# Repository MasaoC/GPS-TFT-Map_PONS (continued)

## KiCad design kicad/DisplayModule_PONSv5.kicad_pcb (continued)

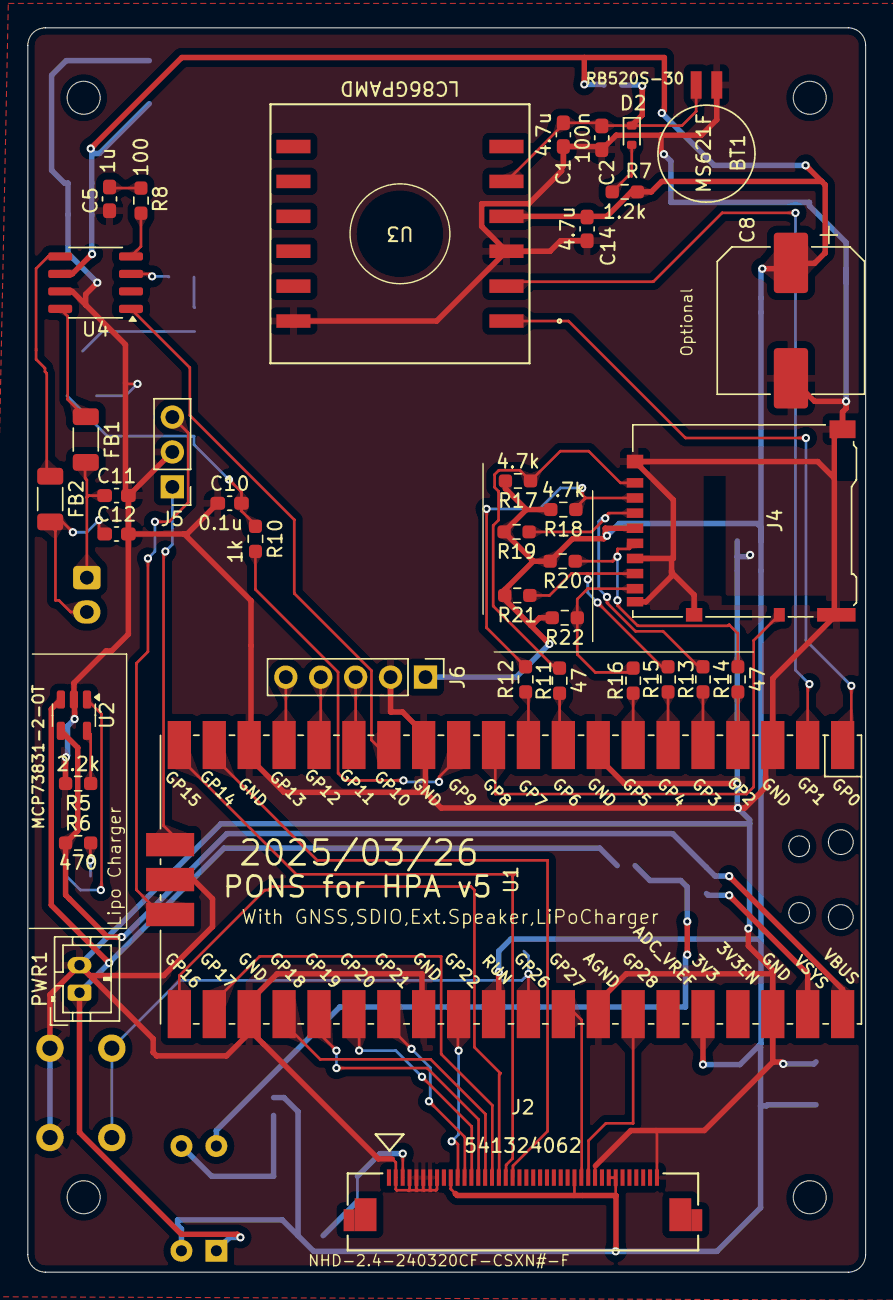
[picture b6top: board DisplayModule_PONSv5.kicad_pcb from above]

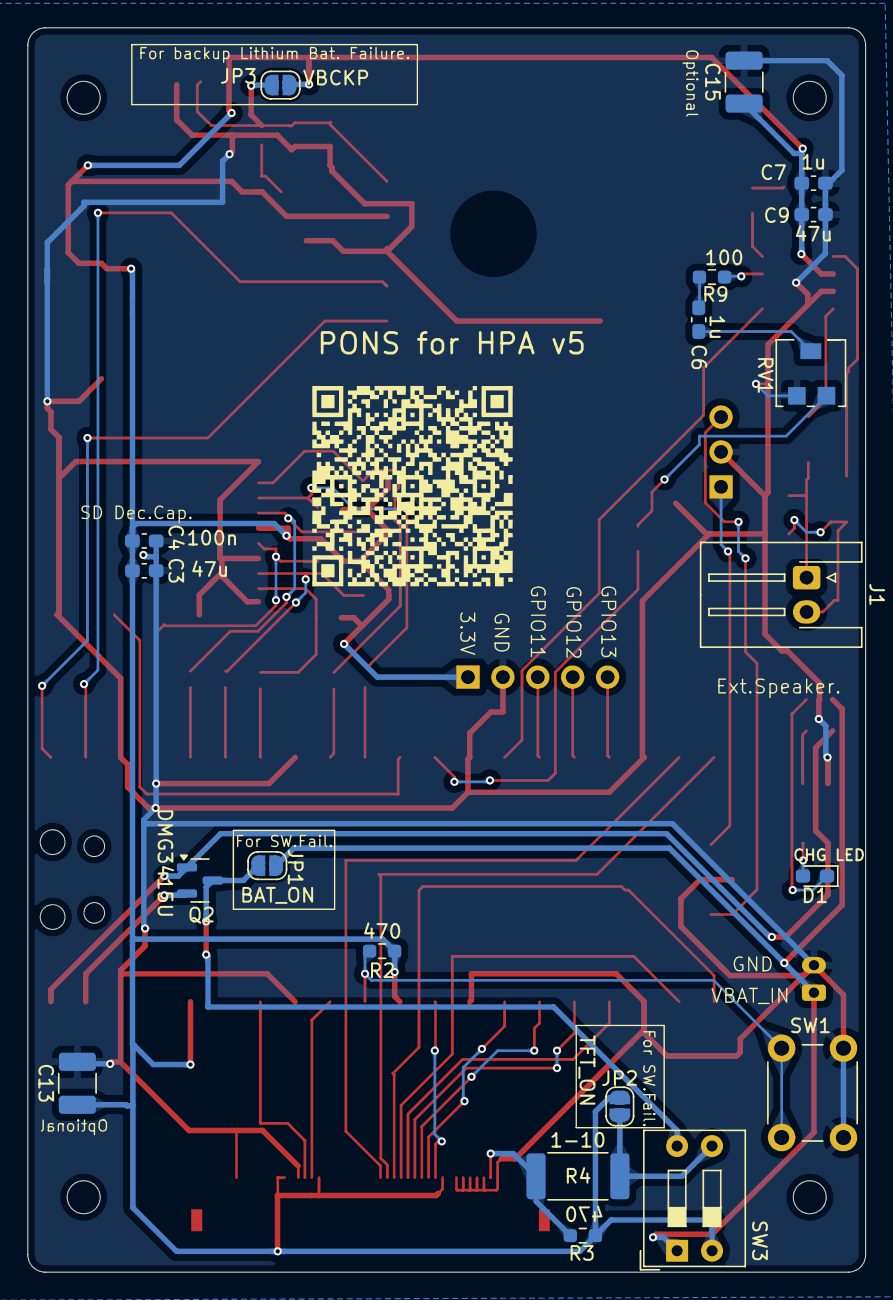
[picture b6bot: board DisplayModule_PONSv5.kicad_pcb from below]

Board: 2 copper layers, 61.0 x 90.5 mm, 58 parts (20 on the bottom side), 57 nets.

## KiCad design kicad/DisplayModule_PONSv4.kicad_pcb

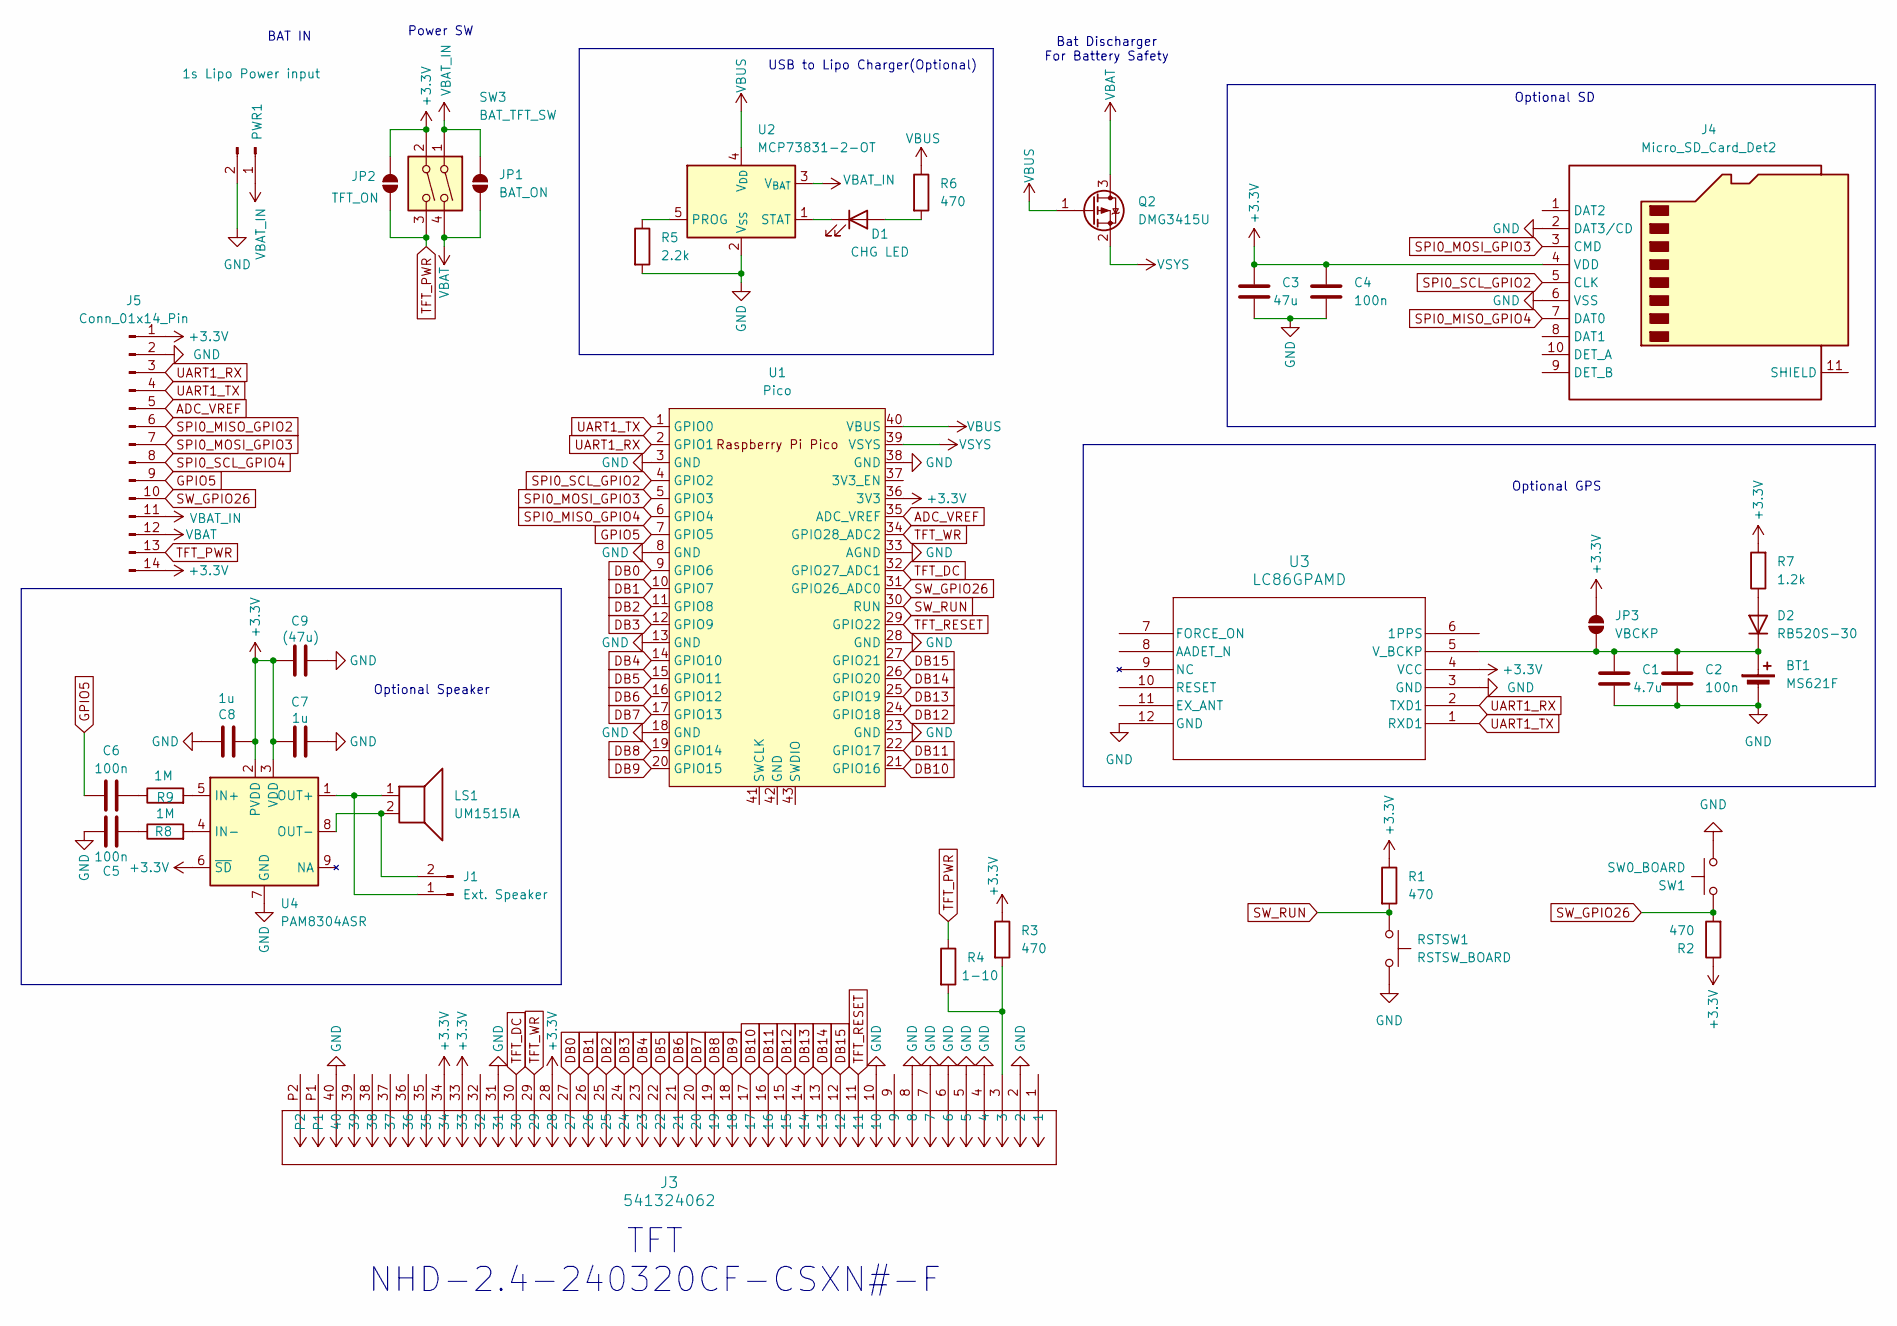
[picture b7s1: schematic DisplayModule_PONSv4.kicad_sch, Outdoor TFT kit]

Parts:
BT1: MS621F; BatteryHolder_Seiko_MS621F
C1: 4.7u; C_0603_1608Metric_Pad1.08x0.95mm_HandSolder
C2, C4, C5, C6: 100n; C_0603_1608Metric_Pad1.08x0.95mm_HandSolder
C3: 47u; C_0603_1608Metric_Pad1.08x0.95mm_HandSolder
C7, C8: 1u; C_0603_1608Metric_Pad1.08x0.95mm_HandSolder
C9: (47u); C_0603_1608Metric_Pad1.08x0.95mm_HandSolder
D1: CHG LED; LED_0603_1608Metric_Pad1.05x0.95mm_HandSolder
D2: RB520S-30; D_SOD-523
J1: Ext. Speaker; JST_XA_B02B-XASK-1_1x02_P2.50mm_Vertical
J3: 541324062; CON_541324062_MOL
J4: Micro_SD_Card_Det2; microSD_HC_Hirose_DM3AT-SF-PEJM5
J5: Conn_01x14_Pin; PinHeader_1x14_P2.54mm_Vertical
JP1: BAT_ON; SolderJumper-2_P1.3mm_Open_RoundedPad1.0x1.5mm
JP2: TFT_ON; SolderJumper-2_P1.3mm_Open_RoundedPad1.0x1.5mm
JP3: VBCKP; SolderJumper-2_P1.3mm_Open_RoundedPad1.0x1.5mm
LS1: UM1515IA; UM1515IA085008
PWR1: 1s Lipo Power input; JST_PH_B2B-PH-K_1x02_P2.00mm_Vertical
Q2: DMG3415U; SOT-23
R1, R2, R3, R6: 470; R_0603_1608Metric_Pad0.98x0.95mm_HandSolder
R4: 1-10; R_2512_6332Metric_Pad1.40x3.35mm_HandSolder
R5: 2.2k; R_0603_1608Metric_Pad0.98x0.95mm_HandSolder
R7: 1.2k; R_0603_1608Metric_Pad0.98x0.95mm_HandSolder
R8, R9: 1M; R_0603_1608Metric_Pad0.98x0.95mm_HandSolder
RSTSW1: RSTSW_BOARD; TVAF06-A020B-R
SW1: SW0_BOARD; SW_PUSH_6mm_H9.5mm
SW3: BAT_TFT_SW; SW_DIP_SPSTx02_Slide_9.78x7.26mm_W7.62mm_P2.54mm
U1: Pico; RPi_Pico_SMD
U2: MCP73831-2-OT; SOT-23-5
U3: LC86GPAMD; L86_QWS
U4: PAM8304ASR; MSOP-8-1EP_3x3mm_P0.65mm_EP1.5x1.8mm

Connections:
+3.3V: C3.1, C4.1, C7.1, C8.1, C9.1, J3.28, J3.33, J3.34, J4.4 (VDD), J5.1, J5.14, JP2.2 (B), JP3.1 (A), R1.1, R2.1, R3.1, R7.2, SW3.2, U1.36 (3V3), U3.4 (VCC), U4.2 (PVDD), U4.3 (VDD), U4.6 (~SD)
ADC_VREF: J5.5, U1.35 (ADC_VREF)
DB0: J3.27, U1.9 (GPIO6)
DB1: J3.26, U1.10 (GPIO7)
DB2: J3.25, U1.11 (GPIO8)
DB3: J3.24, U1.12 (GPIO9)
DB4: J3.23, U1.14 (GPIO10)
DB5: J3.22, U1.15 (GPIO11)
DB6: J3.21, U1.16 (GPIO12)
DB7: J3.20, U1.17 (GPIO13)
DB8: J3.19, U1.19 (GPIO14)
DB9: J3.18, U1.20 (GPIO15)
DB10: J3.17, U1.21 (GPIO16)
DB11: J3.16, U1.22 (GPIO17)
DB12: J3.15, U1.24 (GPIO18)
DB13: J3.14, U1.25 (GPIO19)
DB14: J3.13, U1.26 (GPIO20)
DB15: J3.12, U1.27 (GPIO21)
GND: BT1.2 (-), C1.2, C2.2, C3.2, C4.2, C5.1, C7.2, C8.2, C9.2, J3.2, J3.4, J3.5, J3.6, J3.7, J3.8, J3.10, J3.31, J3.40, J4.2 (DAT3/CD), J4.6 (VSS), J5.2, PWR1.2, R5.2, RSTSW1.2, SW1.2, U1.3 (GND), U1.8 (GND), U1.13 (GND), U1.18 (GND), U1.23 (GND), U1.28 (GND), U1.33 (AGND), U1.38 (GND), U2.2 (V_{SS}), U3.3 (GND), U3.12 (GND), U4.7 (GND)
GPIO5: C6.1, J5.9, U1.7 (GPIO5)
unnamed: BT1.1 (+), C1.1, C2.1, D2.1 (K), JP3.2 (B), U3.5 (V_BCKP)
unnamed: C5.2, R8.1
unnamed: C6.2, R9.1
unnamed: D1.2 (A), R6.2
unnamed: D1.1 (K), U2.1 (STAT)
unnamed: D2.2 (A), R7.1
unnamed: J1.1, LS1.1, U4.1 (OUT+)
unnamed: J1.2, LS1.2, U4.8 (OUT-)
unnamed: J3.3, R3.2, R4.2
unnamed: R5.1, U2.5 (PROG)
unnamed: R9.2, U4.5 (IN+)
unnamed: R8.2, U4.4 (IN-)
SPI0_MISO_GPIO2: J5.6
SPI0_MISO_GPIO4: J4.7 (DAT0), U1.6 (GPIO4)
SPI0_MOSI_GPIO3: J4.3 (CMD), J5.7, U1.5 (GPIO3)
SPI0_SCL_GPIO2: J4.5 (CLK), U1.4 (GPIO2)
SPI0_SCL_GPIO4: J5.8
SW_GPIO26: J5.10, R2.2, SW1.1, U1.31 (GPIO26_ADC0)
SW_RUN: R1.2, RSTSW1.1, U1.30 (RUN)
TFT_DC: J3.30, U1.32 (GPIO27_ADC1)
TFT_PWR: J5.13, JP2.1 (A), R4.1, SW3.3
TFT_RESET: J3.11, U1.29 (GPIO22)
TFT_WR: J3.29, U1.34 (GPIO28_ADC2)
UART1_RX: J5.3, U1.2 (GPIO1), U3.2 (TXD1)
UART1_TX: J5.4, U1.1 (GPIO0), U3.1 (RXD1)
VBAT: J5.12, JP1.2 (B), Q2.3 (D), SW3.4
VBAT_IN: J5.11, JP1.1 (A), PWR1.1, SW3.1, U2.3 (V_{BAT})
VBUS: Q2.1 (G), R6.1, U1.40 (VBUS), U2.4 (V_{DD})
VSYS: Q2.2 (S), U1.39 (VSYS)

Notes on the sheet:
Optional SD
Optional GPS
USB to Lipo Charger(Optional)
Bat Discharger For Battery Safety
BAT IN
Optional Speaker
Power SW
TFT NHD-2.4-240320CF-CSXN#-F

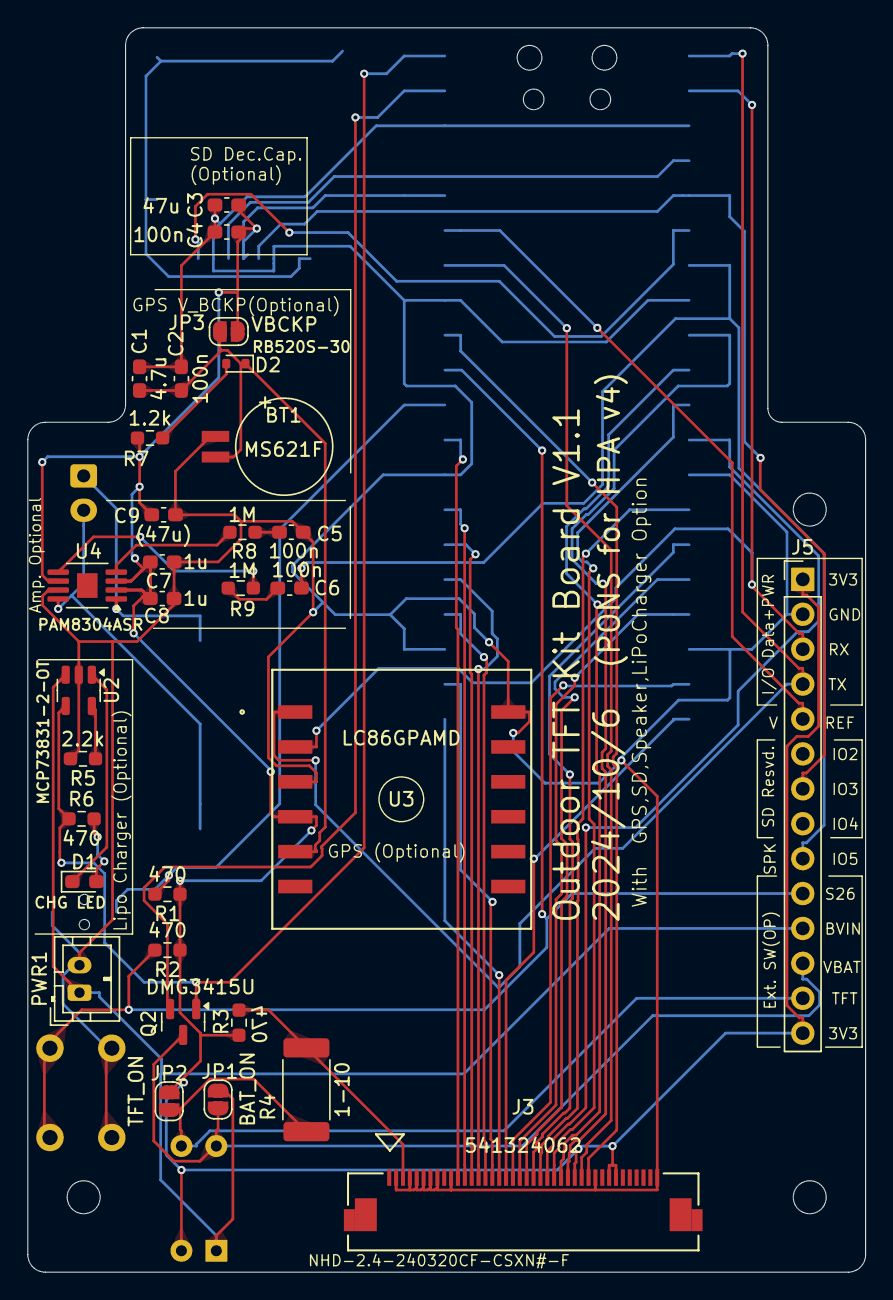
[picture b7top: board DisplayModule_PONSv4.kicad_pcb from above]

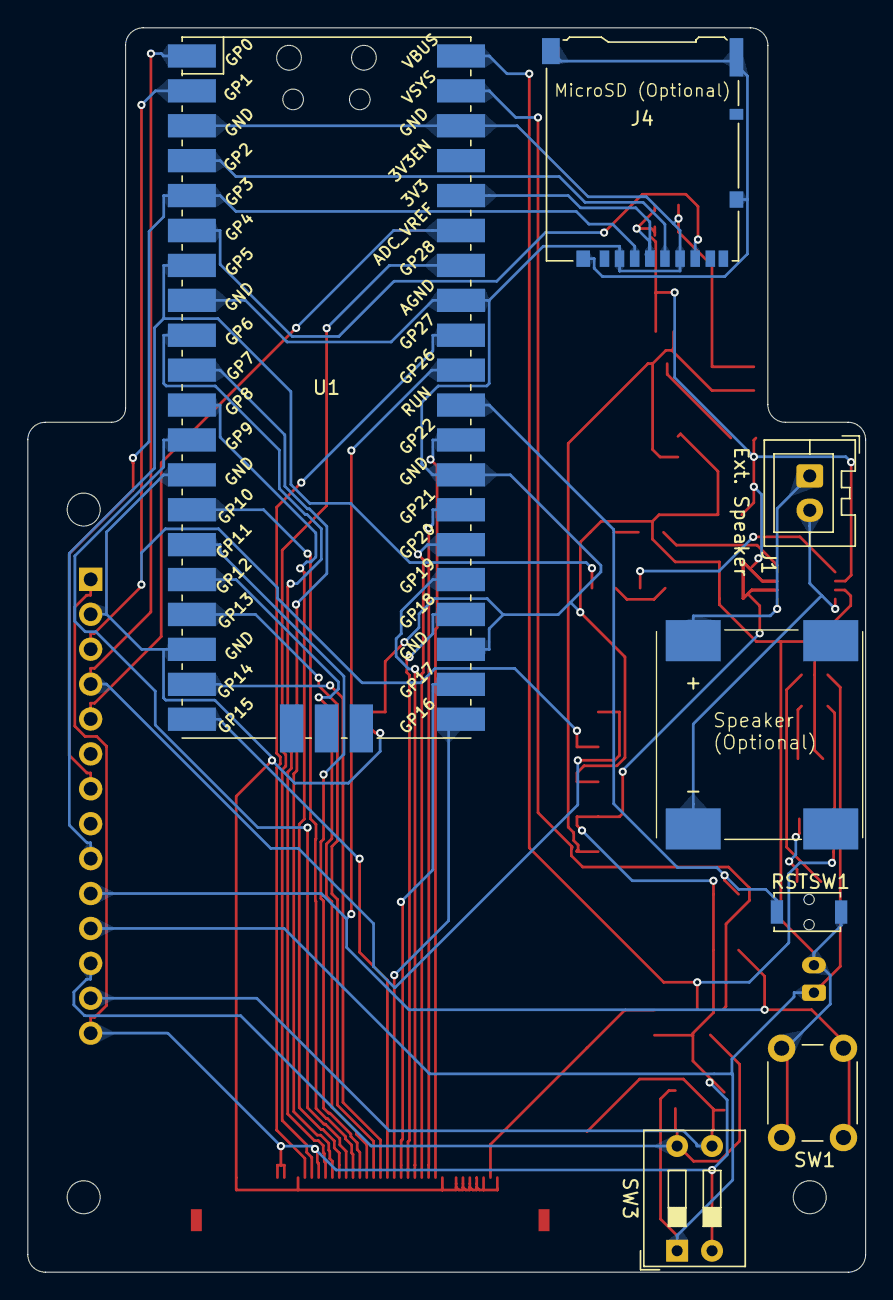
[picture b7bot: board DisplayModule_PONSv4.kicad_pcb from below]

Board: 2 copper layers, 61.0 x 90.5 mm, 38 parts (7 on the bottom side), 47 nets.

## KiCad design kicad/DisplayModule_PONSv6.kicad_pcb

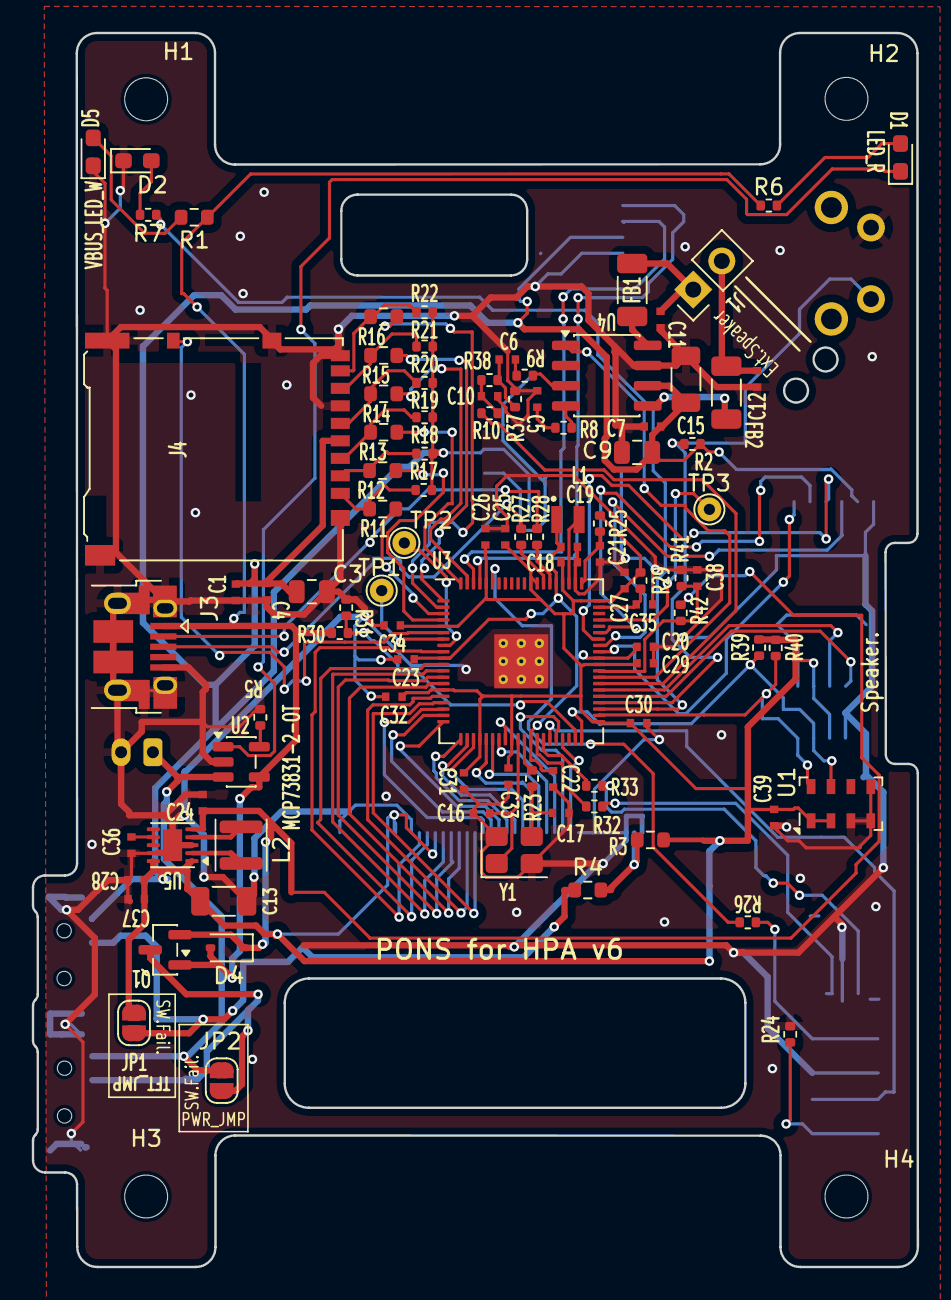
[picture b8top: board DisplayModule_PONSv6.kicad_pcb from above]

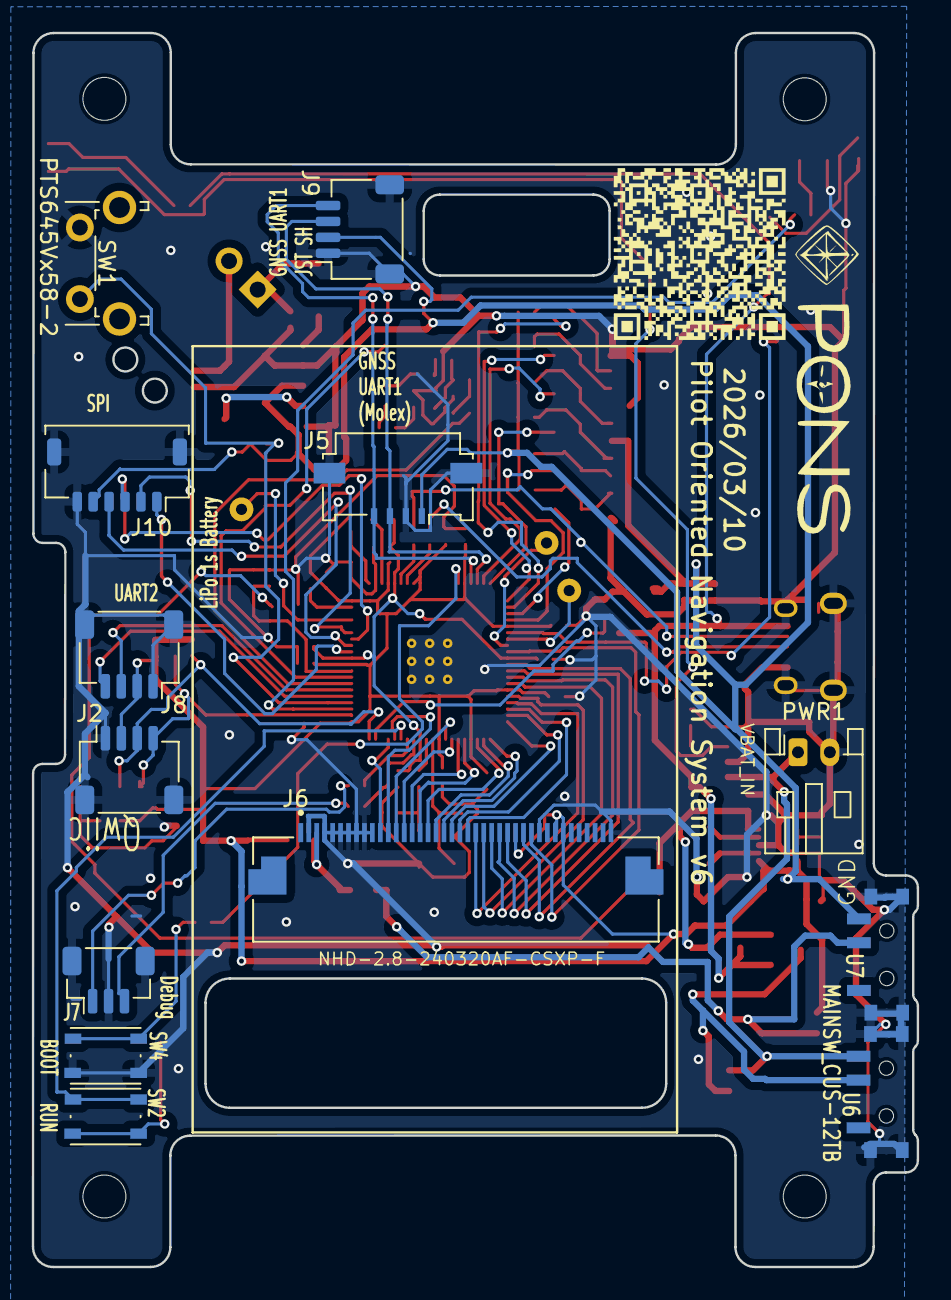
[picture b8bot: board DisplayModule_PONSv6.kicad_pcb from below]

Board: 2 copper layers, 55.6 x 77.6 mm, 115 parts (13 on the bottom side), 96 nets.

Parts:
C1, C5, C6, C7, C38: 1u; C_0402_1005Metric_small_pads
C3, C9: 47u; C_0805_2012Metric
C4, C10, C20, C23, C25, C26, C27, C29, C30, C31, C32, C33, C34, C36, C39: 100n; C_0402_1005Metric_small_pads
C11, C12: 220p; C_0402_1005Metric_small_pads
C13, C15: 100u; C_1206_3216Metric
C16, C17: 33p; C_0402_1005Metric_small_pads
C18, C19, C21, C22, C24, C35: 4.7u; C_0402_1005Metric_small_pads
C28, C37: 10u; C_0402_1005Metric_small_pads
D1, D2: LED_R; LED_0603_1608Metric_Pad1.05x0.95mm_HandSolder
D4: 1N5819WS; D_SOD-323
D5: VBUS_LED_W; LED_0603_1608Metric_Pad1.05x0.95mm_HandSolder
FB1, FB2: 390; L_1206_3216Metric_Pad1.22x1.90mm_HandSolder
H1, H2, H3, H4: MountingHole; MountingHole_2.7mm_M2.5
J1: Ext. Speaker; PinHeader_1x02_P2.54mm_Vertical
J2, J9: Conn_01x04_MountingPin; JST_SH_SM04B-SRSS-TB_1x04-1MP_P1.00mm_Horizontal
J3: USB_B_Micro; USB_Micro-B_Amphenol_10103594-0001LF_Horizontal
J4: Micro_SD_Card_Det2; microSD_HC_Hirose_DM3AT-SF-PEJM5
J5: 2005280040; Molex_200528-0040_1x04-1MP_P1.00mm_Horizontal
J6: 54132-4062; MOLEX_54132-4062
J7: Conn_01x03_Shielded; JST_SH_BM03B-SRSS-TB_1x03-1MP_P1.00mm_Vertical
J8: Conn_01x04_Shielded; JST_SH_SM04B-SRSS-TB_1x04-1MP_P1.00mm_Horizontal
J10: Conn_01x05_MountingPin; JST_SHL_SM06B-SHLS-TF_1x06-1MP_P1.00mm_Horizontal
JP1: TFT_JMP; SolderJumper-2_P1.3mm_Open_RoundedPad1.0x1.5mm
JP2: PWR_JMP; SolderJumper-2_P1.3mm_Open_RoundedPad1.0x1.5mm
L1: 3.3u; L_pol_2016
L2: 1.5u; L_APV_ANR3015
PWR1: 1s Lipo Power input; JST_PH_S2B-PH-K_1x02_P2.00mm_Horizontal
Q1: AO3401A; SOT-23
R1, R3: 470; R_0603_1608Metric
R2: 470; R_0402_1005Metric
R4: 1; R_0603_1608Metric
R5: 2.2k; R_0402_1005Metric
R6, R7, R29: 200; R_0402_1005Metric
R8, R9, R32, R33: 100; R_0402_1005Metric
R10, R23, R24, R26, R38: 1k; R_0402_1005Metric
R11, R12, R13, R14, R15, R16: 47; R_0603_1608Metric
R17, R18, R19, R20, R21, R22, R39, R40: 4.7k; R_0402_1005Metric
R25: 33; R_0402_1005Metric
R27, R28: 22; R_0402_1005Metric
R30: 5K1; R_0402_1005Metric
R31: 10K; R_0402_1005Metric
R37: 10k; R_0402_1005Metric
R41: 51K; R_0402_1005Metric
R42: 100K; R_0402_1005Metric
SW1: PTS645Vx58-2; SW_Tactile_SPST_Angled_PTS645Vx58-2LFS
SW2: SW_Push_RUN; SW_Push_1P1T_NO_Vertical_Wuerth_434133025816
SW4: SW_Push_BOOT; SW_Push_1P1T_NO_Vertical_Wuerth_434133025816
TP1, TP2, TP3: TestPoint; TestPoint_THTPad_D1.5mm_Drill0.7mm
U1: MS5611-01BA; LGA-8_3x5mm_P1.25mm
U2: MCP73831-2-OT; SOT-23-5
U3: RP2350_80QFN; RP2350-QFN-80-1EP_10x10_P0.4mm_EP3.4x3.4mm_ThermalVias
U4: PAM8302AAD; SO-8_3.9x4.9mm_P1.27mm
U5: TPS63031DSK; WSON-10-1EP_2.5x2.5mm_P0.5mm_EP1.2x2mm
U6: MAINSW_CUS-12TB; CUS-12B
U7: TFTSW_CUS-12TB; CUS-12B
Y1: X322512MSB4SI; Crystal_SMD_3225-4Pin_3.2x2.5mm

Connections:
+1V1: C19.1, C20.1, C22.1, C23.1, L1.1, U3.10 (DVDD), U3.32 (DVDD), U3.51 (DVDD), U3.65 (VREG_FB)
+3V3: C1.1, C3.1, C4.1, C7.1, C9.1, C13.1, C15.1, C18.1, C25.1, C26.1, C27.1, C28.1, C29.1, C30.1, C31.1, C32.1, C33.1, C34.1, C37.1, C39.1, J2.2, J4.4 (VDD), J5.1, J6.28, J6.33, J6.34, J8.2, J9.2, J10.5, JP1.2 (B), R2.1, R3.1, R17.2, R18.2, R19.2, R20.2, R21.2, R22.2, R25.1, R29.1, R39.1, R40.1, U1.1 (VDD), U1.2 (PS), U3.5 (IOVDD), U3.15 (IOVDD), U3.24 (IOVDD), U3.29 (IOVDD), U3.41 (IOVDD), U3.50 (IOVDD), U3.60 (IOVDD), U3.64 (VREG_VIN), U3.68 (USB_OTP_VDD), U3.69 (QSPI_IOVDD), U3.76 (IOVDD), U4.6 (VDD), U5.1 (VOUT), U5.10 (FB), U7.P$3 (3)
/RP2354B/RUN: SW2.2, U3.35 (RUN)
/RP2354B/USB_D+: J3.3 (D+), R27.1
/RP2354B/USB_D-: J3.2 (D-), R28.1
/RP2354B/VREG_AVDD: C21.1, R25.2, U3.61 (VREG_AVDD)
/RP2354B/VREG_LX: L1.2, U3.63 (VREG_LX)
/RP2354B/XIN: C16.1, U3.30 (XIN), Y1.1
/RP2354B/XOUT: R23.1, U3.31 (XOUT)
/RP2354B/~USB_BOOT: R26.2, SW4.2
AMP_SD: U3.48 (GPIO39), U4.1 (~SD)
BATPWR_LDO: JP2.1 (A), Q1.3 (D), U6.P$2 (2)
DB0: J6.27, U3.12 (GPIO13)
DB1: J6.26, U3.13 (GPIO14)
DB2: J6.25, U3.14 (GPIO15)
DB3: J6.24, U3.16 (GPIO16)
DB4: J6.23, U3.17 (GPIO17)
DB5: J6.22, U3.18 (GPIO18)
DB6: J6.21, U3.19 (GPIO19)
DB7: J6.20, U3.20 (GPIO20)
DB8: J6.19, U3.21 (GPIO21)
DB9: J6.18, U3.22 (GPIO22)
DB10: J6.17, U3.23 (GPIO23)
DB11: J6.16, U3.25 (GPIO24)
DB12: J6.15, U3.26 (GPIO25)
DB13: J6.14, U3.27 (GPIO26)
DB14: J6.13, U3.28 (GPIO27)
DB15: J6.12, U3.36 (GPIO28)
GND: C1.2, C3.2, C4.2, C5.1, C7.2, C9.2, C10.1, C11.2, C12.2, C13.2, C15.2, C16.2, C17.2, C18.2, C19.2, C20.2, C21.2, C22.2, C23.2, C24.2, C25.2, C26.2, C27.2, C28.2, C29.2, C30.2, C31.2, C32.2, C33.2, C34.2, C35.2, C36.2, C37.2, C38.2, C39.2, D2.1 (K), D5.1 (K), J2.1, J2.MP (MountPin), J3.5 (GND), J3.6 (Shield), J4.6 (VSS), J4.9 (DET_B), J4.11 (SHIELD), J5.2, J5.MP, J6.2, J6.4, J6.5, J6.6, J6.7, J6.8, J6.9, J6.10, J6.31, J6.40, J7.2, J7.MP (Shield), J8.1, J8.MP (Shield), J9.1, J9.MP (MountPin), J10.6, J10.MP (MountPin), PWR1.2, R5.2, R24.2, R31.2, R37.1, R41.2, SW1.2, SW4.1, U1.3 (GND), U1.4 (CSB), U1.5 (CSB), U2.2 (V_{SS}), U3.62 (VREG_PGND), U3.81 (GND), U4.7 (GND), U5.3 (PGND)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
I2C0_SCL: J8.4, R40.2, U1.8 (SCLK), U3.42 (GPIO33)
I2C0_SDA: J8.3, R39.2, U1.7 (SDI/SDA), U3.40 (GPIO32)
unnamed: C5.2, R8.1
unnamed: C6.1, R37.2, R38.1
unnamed: C6.2, R9.1
unnamed: C10.2, R10.1, R38.2
unnamed: C17.1, R23.2, Y1.3
unnamed: D1.2 (A), R6.2
unnamed: D1.1 (K), U2.1 (STAT)
unnamed: D2.2 (A), R7.2
unnamed: D5.2 (A), R1.2
unnamed: C11.1, FB1.2, J1.1
unnamed: C12.1, FB2.2, J1.2
unnamed: J4.5 (CLK), R14.2, R20.1
unnamed: J4.3 (CMD), R13.2, R19.1
unnamed: J4.7 (DAT0), R15.2, R21.1
unnamed: J4.8 (DAT1), R16.2, R22.1
unnamed: J4.1 (DAT2), R11.2, R17.1
unnamed: J4.2 (DAT3/CD), R12.2, R18.1
unnamed: J6.3, R3.2, R4.2
unnamed: J7.1, R33.2
unnamed: J7.3, R32.2
unnamed: R24.1, SW2.1
unnamed: R5.1, U2.5 (PROG)
unnamed: C35.1, R29.2, U3.59 (ADC_AVDD)
unnamed: TP1.1, U3.7 (GPIO9)
unnamed: TP2.1, U3.8 (GPIO10)
unnamed: C38.1, R41.1, R42.2, U3.49 (GPIO40_ADC0)
unnamed: TP3.1, U3.57 (GPIO46_ADC6)
unnamed: R26.1, U3.75 (QSPI_SS)
unnamed: R32.1, U3.33 (SWCLK)
unnamed: R33.1, U3.34 (SWD)
unnamed: R28.2, U3.66 (USB_DM)
unnamed: R27.2, U3.67 (USB_DP)
unnamed: R9.2, U4.3 (IN+)
unnamed: R8.2, U4.4 (IN-)
unnamed: FB2.1, U4.5 (OUT+)
unnamed: FB1.1, U4.8 (OUT-)
unnamed: C36.1, U5.6 (EN), U5.7 (PS/SYNC), U5.8 (VINA)
unnamed: L2.1, U5.4 (L1)
unnamed: L2.2, U5.2 (L2)
PWM_AUDIO: R10.2, U3.47 (GPIO38)
PWR_TFT: JP1.1 (A), R4.1, U7.P$2 (2)
SD_CLK: R14.1, U3.79 (GPIO2)
SD_CMD: R13.1, U3.80 (GPIO3)
SD_DAT0: R15.1, U3.1 (GPIO4)
SD_DAT1: R16.1, U3.2 (GPIO5)
SD_DAT2: R11.1, U3.3 (GPIO6)
SD_DAT3: R12.1, U3.4 (GPIO7)
SD_DETA: J4.10 (DET_A), U3.6 (GPIO8)
SPI1_CS: J10.1, U3.52 (GPIO41_ADC1)
SPI1_RX: J10.2, U3.55 (GPIO44_ADC4)
SPI1_SCK: J10.4, U3.53 (GPIO42_ADC2)
SPI1_TX: J10.3, U3.54 (GPIO43_ADC3)
SW_TOGGLE: R2.2, SW1.1, U3.44 (GPIO35)
TFT_DC: J6.30, U3.9 (GPIO11)
TFT_RESET: J6.11, U3.37 (GPIO29)
TFT_WR: J6.29, U3.11 (GPIO12)
UART0_RX: J5.3, J9.3, U3.78 (GPIO1)
UART0_TX: J5.4, J9.4, U3.77 (GPIO0)
UART1_RX: J2.3, U3.46 (GPIO37)
UART1_TX: J2.4, U3.45 (GPIO36)
USB_SENS: R30.2, R31.1, U3.39 (GPIO31)
USR_LED: R7.1, U3.43 (GPIO34)
VBAT_IN: JP2.2 (B), PWR1.1, U2.3 (V_{BAT}), U6.P$3 (3)
VBUS: D4.2 (A), J3.1 (VBUS), Q1.1 (G), R1.1, R6.1, R30.1, U2.4 (V_{DD})
VSYS: C24.1, D4.1 (K), Q1.2 (S), R42.1, U5.5 (VIN)

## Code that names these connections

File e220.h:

// ============================================================
// File    : e220.h
// Project : PONS v7 — PONS Link
// Role    : E220-900T22S(JP)（920MHz LoRa）の下位ドライバ。
//           UART の叩き方・モード制御・レジスタ設定だけを持ち、
//           テレメトリの意味は一切知らない（それは link.cpp の仕事）。
// Author  : MasaoC (@masao_mobile)
// Updated : 2026/11/07
// ============================================================
//
// ■ 配線（docs/pons_link.md §2）
//     RP2350 GPIO8  (UART1 TX) → E220 RXD
//     RP2350 GPIO9  (UART1 RX) ← E220 TXD
//     RP2350 GPIO30            ← E220 AUX（状態通知）
//     RP2350 GPIO31            → E220 M0+M1（結線して 1 本で駆動）
//
//   M0/M1 は **GPIO31**（ネット LORA_M01。E220 は U9）。GPIO41 は SCH16T の SPI1_CS。
//   2026-10 に GPIO47 から移した（GPIO47 は ADC が使えるので USB_SENS に回した）。
//   M0 と M1 を 1 本で駆動する（5 番と 6 番が同じネット）。
//
// ■ モードは 2 つしか使わない
//     mode 0 (LOW)  : 通常送受信。受信待機 8.2mA
//     mode 3 (HIGH) : Config/DeepSleep。2.5µA
//   WOR は使わないので M0/M1 を分ける必要が無い（データシート 5.3）。
//
// ■ 送信機は寝かせる、受信機は寝かせない
//   受信機を寝かせるにはスロット同期が要るが、常時受信でも 8.2mA しか
//   食わないので当面やらない。送信機は UART へ流し込んだ直後に
//   mode 3 へ落とすだけでよい（高速スリープ）。→ docs/pons_link.md §3
//
#ifndef E220_H
#define E220_H

#include <Arduino.h>
#include <stdint.h>
#include "settings.h"

// ---- ピン ----
#define E220_AUX_PIN     30      // 状態通知（Low = 処理中 / High = アイドル）
#define E220_TX_PIN       8      // RP2350 → E220 RXD
#define E220_RX_PIN       9      // RP2350 ← E220 TXD

// M0+M1（GPIO31）。**この無線専用のピン。** ほかのコードから駆動すると E220 が mode 3
// （Config/DeepSleep）へ落ちて無線が黙る（v7 で IMU の初期化から触って実際に起きた）。
  #define E220_MODE_PIN  31

// ---- ラジオ設定 ----
// radio_profile → 拡散率。SF を上げるほど 2.5dB ずつ強くなるが、
// 送信時間（＝送信電流）が倍々に増える。既定は SF8。
#define E220_SF_MIN       7
#define E220_SF_MAX      11
// 帯域幅は 500kHz 固定（CH の番号と周波数の対応もこれが前提。docs/pons_link.md §2）。変更手段は無い。
// ※ 以前は WIRELESS 画面の SF 行に出していたが、変えられない値を毎回出しても
//   情報にならないので、そこは送信時間と電波占有率（e220_airtime_ms）へ譲った。
//   この定数は仕様の記録として残してある。
#define E220_BW_KHZ     500
#define E220_CH_MAX      12      // 923.2MHz。ここまでが休止 50ms 固定の帯域（ローワーバンド）
// BW500kHz のチャンネルの上限（データシート 表15。926.8MHz）。CH13 から上がアッパーバンド。
// ★ アッパーで送れるのは E220_UPPER_MAX_PAYLOAD バイトまで（1 パケットが 32 バイトに固定される）。
//   上位はどの CH でも 32 バイトのフレーム（lora_link/link_wire2.h）で送る。それを超えるものは e220_send が断る。
//   休止（送信時間の 10 倍）に合わせた送る間隔は link.cpp が守る（link_tx_period_ms）。
#define E220_CH_MAX_ALL        30
#define E220_UPPER_MAX_PAYLOAD 32

uint8_t e220_profile_to_sf(uint8_t profile);   // 0→SF7 … 4→SF11

// ---- ライフサイクル ----
// UART を開き、モジュールへ設定を書き、読み返して照合する。
// 失敗しても戻ってくる（e220_alive() が false になるだけ）。
void e220_setup(uint8_t ch, uint8_t profile);

// 設定画面からチャンネル/プロファイルが変わったときに呼ぶ。
// mode 3 へ入って書き直し、mode 0 へ戻す。
//
// ★ persist で書込みコマンドを選ぶ。
//     true  … 0xC0（不揮発）。**書換え寿命がある**ので起動時の 1 回だけ。
//     false … 0xC2（RAM のみ）。設定画面で値を回している間はこちら。
//   設定の正本は SD の settings.txt なので、RAM に書くだけでも
//   次回起動時に同じ値が復元される。CH を一周させるだけで何回も
//   フラッシュに書くのは、モジュールの寿命を無駄に削るだけになる。
// ch は E220_CH_MAX_ALL まで（アッパーバンドも受け付ける。サブパケット長はどの CH でも 32B）。
bool e220_reconfigure(uint8_t ch, uint8_t profile, bool persist);

// モジュールが生きているか。次の 2 つを **両方** 満たすときだけ true。
//   ・起動時（または設定変更時）の書き込み→読み返しの照合が通っている
//   ・直近の問い合わせに返事がある（連続して無応答なら false へ落ちる）
// ★ 後者が要る。照合は e220_setup() / e220_reconfigure() でしか行われないので、
//   それだけだと **飛行中にコネクタが抜けても true のまま**になり、
//   送信機は「送れているつもり」で飛び続ける（上りが無いので気づけない）。
//   返事の有無は e220_read_noise() と e220_recv() が内部で数えている。
//   送信機は寝ている時間が長く自然な機会が無いので、link.cpp が定期的に叩く。
bool e220_alive();

// ---- 送受信 ----
// n バイトを 1 パケットとしてブロードキャスト送信する。
//   ★ write() はハード FIFO が空くまでスピンする（arduino-pico 4.5.1 で確認済。
//     送信側にソフトバッファは無く、setFIFOSize() が効くのは受信側だけ）。
//     115200bps で 35 バイト（32 + 宛先 3）なら FIFO にほぼ収まり、ブロックは 0.3ms ほど
//     （65 バイトの頃の 68 バイトで約 3.1ms）。ブロックするおかげで
//     バイト列に隙間ができず、E220 にパケットを分割されない（§4）。
bool e220_send(const uint8_t* payload, uint8_t n);

// 受信バイトを取り込み、完全な 1 パケットが揃ったら true。
// 毎ループ呼ぶこと。frame_len バイトのペイロードと RSSI 1 バイトを想定する。
// frame_len は LINK_W2_LEN（32 バイトのフレーム。印は lora_link/link_wire2.h の LINK_W2_MAGIC）。それ以外は false。
// ★ GNSS の時刻の助け合いのビーコン（印 0x58。lora_link/link_beacon.h。2026-11-13〜）も同じ長さなので一緒に返す。
//   diagnose_formats が真なら、CRC の通った既知の旧形式も診断用に返す。呼び出し側が印で見分ける。
bool e220_recv(uint8_t* out, uint8_t frame_len, int16_t* rssi_dbm, bool diagnose_formats);

// 印は合ったが CRC の検証に落ちたフレームの累計。
// 「電波は届いたが化けている」と「そもそも来ていない」を区別する診断用。
uint32_t e220_bad_frames();

// 32 バイトのペイロード 1 回ぶんの送信時間 [ms]（BW500kHz。見積もり）。
// ローワーの 1Hz 運用なら /10 が占有率 [%]（アッパーは送る間隔が長いので link.cpp で割る）。
// SF を上げると感度が 2.5dB 上がる代わりにここが約 1.8 倍になるので、
// 設定画面で SF を選ぶその場に出して代償を見せるために使う。
uint16_t e220_airtime_ms(uint8_t profile);

// ---- 省電力 ----
void e220_sleep();     // mode 3 へ。送信中なら送信完了後に入る
void e220_wake();      // mode 0 へ。復帰を**待つ**（最大 50ms Core0 が止まる）
// mode 0 のまま状態レジスタ読み出しが噛み合わなくなったときに、mode 3 → mode 0 を
// 1 回だけ経由して立て直す（CH SCAN の初手無応答時の復帰用。最大 ~60ms）。
void e220_cycle_normal();

// ---- ノンブロッキング起床（1Hz の定期送信用）----
// e220_wake() は AUX の立ち上がりを待つので、毎秒それをやると Core0 が
// その分止まる。送信は「起こす → 起きたら送る → 送り切ったら寝かす」の
// 3 手に分ければ待たずに済む。使い方は link.cpp の link_tx_tick() を見ること。
//   e220_wake_begin()  … mode 0 にするだけ。**待たない**
//   e220_wake_ready()  … 起きたら true（AUX が High になった）。**待たない**
void e220_wake_begin();
bool e220_wake_ready();

// ---- 診断 ----
// 環境ノイズ [dBm]。距離を決めているのはこれ（docs/pons_link.md §8）。
// mode 0 で呼ぶこと（mode 3 では常に false）。
// ★ **生存確認を兼ねる。** モジュールへの唯一の往復なので、返事の有無が
//   そのまま e220_alive() に効く。値が要らない場面で叩いてもよい。
//   応答待ちは生きていれば数 ms。無応答が続く間は待ちを 30ms へ詰めるので、
//   繰り返し呼んでも Core0 を長く止めない。
// 生存確認（レジスタを 1 バイト読むだけ。電波は出さない）。
// mode 3 へ潜るので、受信中に呼ばないこと（呼び出し側が link_is_receiving() で除く）。
// 潜っている間は受信できない。所要は set_mode の AUX 待ちとボーレート切替を含めて
// 数十 ms。10 秒に 1 回しか呼ばない前提。
bool e220_ping();

bool e220_read_noise(int16_t* noise_dbm, int16_t* last_rssi_dbm);

// UART に届いた総バイト数（累計）。受信の切り分け用。
// 1 フレーム = sizeof(LinkTelem) + RSSI 1 バイト。1Hz なら毎分 66×60 ≒ 3960 増える。
uint32_t e220_rx_bytes();

// 無線モジュールが since_ms（millis()）から今までの間に動いていた（送信・起床・受けたものの出力。AUX Low）か
// （2026-11-13〜）。気圧センサーが送信のたびに外れた値を出すので、その間に測ったサンプルを捨てるのに使う（airdata.cpp）。
// 送ったときは送信時間の見込みぶん先まで「動いている」とみなす。e220_setup() の前・モジュールが無いときは false。
bool e220_rf_active_since(uint32_t since_ms);

#endif // E220_H

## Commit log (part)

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2024-06-21 push
2024-06-21 bug fix
    update
2024-06-21 minor change
2024-06-29 ILI9341
    ILI9341
2024-07-01 demo biwako
2024-07-02 compass
2024-07-02 removed compass
2024-07-03 white background
2024-07-04 RP2040 zero
2024-07-07 parser
2024-07-08 quit stable updated version
2024-07-09 Fonts smooth sprites
2024-07-10 clean up
2024-07-10 Deleted OLED
2024-07-10 warning fix
2024-07-11 TFT_eSPI support for ST7789
2024-07-14 PCP prototype
    Button.
2024-07-15 minor fix
    Single switch adaption.
    Removing old codes.
2024-07-15 mapdata
    merge gps_function and latlon
2024-07-18 Bug fix
    Font files into 1 file
    Bug fix. TFT SPI v.s. UART RX issue fixed.
2024-07-19 Major bug fix
    Bug uart connection with GPS fix
2024-07-25 ver0.2 release
2024-07-30 tools folder
2024-08-03 ver 0.3. update for ublox
    ver 0.3. update for ublox
2024-08-04 Add page to maplist
2024-08-06 hardware v3 adjustments
    ublox GSV parse
    nmea display option
    Voltage detector
    and more
2024-08-11 temporally comit
    bmp drawing
2024-08-15 Ver0.4
    SdFat library adaption.
    Map image display function now available.
    tools/googlemap_api.py added to fetch map image.
    Example mapdata kml, csv updated.
2024-08-16 Release 0.4 rev
    Fixed bugs
2024-08-17 0.4 rev
    MapImage with Track up mode now supported.
    Constelation map updated.
    Mapimage scroll bug fix.
2024-08-28 Ver0.45
    Multicore sd card handling.
    And more. Preparing for ver 0.5
2024-08-30 0.491
2024-09-14 v0.49
    Fixed possible memory leak.
    Changed text size of deg/s.
    Displaying MC.
    Updated setting mode ( Added set destination function and set destination mode)
    Still debugging about loop1 crash after running 1,2 hours.
2024-09-15 a
    temp debug
2024-09-15 test
    Debugged Core0 lacking stack issue.
2024-09-15 Squashed commit of the following:
    commit 273d3e12e4ce5dbd8457224d45a6498dea22b5f4
    Author: Masao Chiguchi <masaochiguchi@gmail.com>
    Date: Sun Sep 15 12:45:36 2024 +0900
    test
    Debugged Core0 lacking stack issue.
    commit c87be28fe4a5df6abd9722a4f1a12aef6a7d1488
2024-09-16 v0.5 release
    Bolder text bolder needle.
    Erased Core1 restart function (Core0 Stack overflow issue resolved)
    Fly away bearing bug at far distance issue fixed.
    Drawing stroke uncommented.
    Minor issue fix
2024-09-22 Update logcsv2kml4earth.py
    Some error catch
2024-09-28 GPS file merged
    ublox and mediatek GPS can be choosed from settings.h file now.
    Some debug of loading image from SD.
2024-10-07 v0.51
    ・GPS LC86G adaption.
    ・NMEA sentence storage 14 lines.
    ・Destination initalization without SD card.
2024-10-19 v0.52
    ・Display Seer_to function added.
    ・Beeping function added.
    ・Bug fix (Serial read hung up)
2024-10-19 minor change and python file updated
    Bigger font, minor adjustments
2024-10-19 v0.59
    version number update
2024-10-26 debugging flash
2024-10-27 0.60
    release 0.60
    bug fix of false tone at +/-TT360
2024-10-28 Document and Kicad for PONSv4 (Software v0.60)
    Document and Kicad for PONSv4 (Software v0.60)
2024-10-28 v4 case
    Hardware v4 case model added.
2025-04-13 PONS v5 major update Software ver0.7
    Build 20250412
    ・Hardware change from Raspberry pi pico to pico2. (Faster CPU and more RAM)
    ・SDIO adaption. Faster SD card. Library changed from SdFat to standard SD lib.
    ・Speaker adaption. Any wav file from sd card (16kHz 8bit) can be played.
    ・Shutdown pin of amplifier installed for saving power.
    ・Any frequency of sin wave can be played now.
2025-04-22 ver 0.80
    ・No more flickering display by using backscreen buffer.
    ・Save load settings.
    ・Layout change of navigation display.
    ・Removed strokerManager and textManager related functions due to backscreen.
    ・Removed bank warning
    ・Refactor by removed unnecessary codes.
2025-04-27 ver 0.81
    ・SD card file detail mode added.
    ・NAV 10km destination automatic update mode added.
    ・wav Voices added.
    ・Scale measure changed from circle to bar.
    ・Lake biwa demo mode updated (track display etc.).
    ・Num sats emphasis when 0. And red bar on header when 0.
2025-04-27 Kicad
    Kicad for hardware v5
2025-04-27 v0.82
    changed settings to release mode
2025-04-29 v0.83
    Course warning
2025-04-29 bug fix
    Cause of bug was stack out of bound.
    so core1_separate_stack = true added
    drawWideLine introduced.
    Course warning introduced.
2025-04-29 v0.83
    refactor codes
2025-04-30 v0.84
    ・fly into magenta arrow Bug fixed.
    ・SD initialize bug fixed by placing Serial.println(""); before setup_sd in setup1.
    ・Refactor code for readability, relocated setup1 loop1 etc....
    ・Replaced to SdFat library for no big reason. Debug purpose.
2025-05-02 0.85 for release
    ・Setting menu文言修正
    ・現在位置の表示の表現を三角形から飛行機に変更。
    ・電圧計算方法微調整。
    ・DEMOモードの飛行経路を微調整。
    ・コース警報でChimeが鳴らないバグ修正。
    ・sdフォルダ追加。SDカードのバックアップ。
2025-05-05 0.86
    QZSS display
    Delete shinura
2025-05-10 0.87
    ・Improve navigation display readability. Bolder needle. Bigger font.
    ・Refactor codes for readability.
2025-05-10 Minor change for 0.87
    Build number update
2025-05-11 minor fix
    minor fix for text location
2025-06-28 Coordinates fix (0.871)
    Change of Platform, pilon, circle coordinates due to official rule release of Japan Birdman rally 2025
2025-06-28 PONSv4 0.601
    Change of coordinates due to official rule release of Japan Birdman Rally 2025.
2025-07-17 大会本番前微調整. 0.872
    ・Auto10kmの折り返し判定時のパイロン誤差を500mとして設定(10.475kmで折り返しモードに入る）
    ・TAKESHIMA,N_PILON,W_PILON設定時に、Auto 10km設定の禁止（設定しようとするとエラー音）
    ・Stabd by ... を Stand by に。Spellミス修正
2025-07-17 PONS v4 本番前微調整
    ・円の大きさが間違っているバグを修正。
    ・バージョン表示
    など
2025-07-17 0.501 大会前微調整
    ・円の半径のCircle radiusバグ修正
    ・バージョン更新
    ・FIFO512にUP
    ・パイロンの座標更新 ２０２５ルール
    ・バージョン更新
2025-07-18 PONS v1 大会前微調整
    Code optimize for v1
    パイロン座標修正
2025-07-18 PONS v4 0.602
    ・大会前微調整
    ・v4以外の設定削除
    ・バッファ1024
    ・core1_separate_stack = true
    ・バグSDカードエラー修正(50MhzSCK速度による不安定さ）
2025-08-05 0.88
    ・Replay mode added.
    ・python file to create NMEA replay file added.
    ・createmovie 2025ver
2025-08-23 File name change
    createmovie_csv2mp4.py
2025-09-23 Bug fixes and improvements for stability.
    ・GNSS CSV not saved every second bug fixed.
    ・SETTING screen modified. Color filled circle to check setting is properly set or not for Bird-man Rally.
    ・GPS setup changed (V_BCKUP low issue.) retry setup when no response.
    ・startup demo modified.
    ・saves GPS altitude.
2025-09-23 0.89
    minor visual change on startup demo.
2025-10-16 minor change
    ・起動時のエフェクト調整。
    ・GNSS接続エラー文言の調整
    ・衛星数、電圧のSD保存を追加
2025-10-24 0.891
    Replay modeの無限再生（ループ化）
2025-10-31 0.892
    ・低電圧を3.4から3.5Vに変更。
    ・リプレイモードのループ対応
2026-02-05 Delete DisplayModule_PONSv5-2025-04-28_003740.zip
    Remove unnecessary file.
2026-02-26 For PONS v6 Add comments
    ・claudeでコメントを追加
    ・airdataファイル追加。現在、工事中。
    ・exFAT対応
2026-03-09 0.9: TRACKUP実装・SAM-M10Q対応・airdata・バグ修正多数
    ### 主な変更内容
    ---
    #### 1. TRACKUP モード 本格実装（display_tft.cpp / GPS_TFT_map.ino）
    - draw_triangle() の TRACKUP 分岐を実装
    - 機体アイコン（固定・常に上向き）
    - True Track 維持針三角形（last_tone_tt を TRACKUP 座標系に変換して表示）
2026-03-10 0.901: GSA解析・垂直速度・SDIO/SPIフォールバック・10bit音声PWM・WAVキュー 他
    新機能
    GPS / NMEA
    gps.cpp/h: GSA文を解析する parseGSA() を実装。フィックス種別（1/2D/3D）・PDOP/HDOP/VDOP・使用PRN（最大12）を取得・格納するgetter群を追加
    gps.cpp: UBLOX専用 UBX-CFG-RATE コマンドで測位レートを2Hz化。ナビ画面では GSV/GSA を0.1Hz、星図画面では1Hzに切り替え
    gps.cpp: GPS FIX 取得時に fixed.wav 再生（SDなければ ド-ミ-ソ 代替チャイム）、SDへのイベントログも追加
    GPS_TFT_map.ino: setup_sd(5→1) に変更。起動時の接触不良による長時間ブロックを防止（回
2026-03-11 0.902: バリオメーター音声・VSI・トリム平均・SD_DETECT修正・バッテリー%表示 他
    ### バリオメーター音声（sound.cpp/h, GPS_TFT_map.ino, button.cpp）
    - update_vario() を新規追加。鉛直速度に応じた音をCore0から100msごとに更新
    - 上昇（>+0.4m/s）: 断続ビープ（700+vspeed*300 Hz、上限2200Hz）
    - 下降（<-0.4m/s）: 連続低音（480-|vspeed|*30 Hz、下限300Hz）
    - タイマー割り込みをWAV > Sinトーン > バリオの優先順位つき構造に変更
    - stopPlayback() / myTone() でバリオ使用中はアンプをOFFにしない
2026-03-11 0.903 RELEASE
    Minor change for debugging.
2026-03-12 0.904: 最大G/S表示（5分保持/全時間）追加・DEMOモード対応
    ## 最大 G/S 表示機能の追加 (gps.cpp / gps.h / display_tft.cpp)
    - 起動後の全時間最大 G/S（maxgs）と直近 5 分保持最大 G/S（maxgs_5min）を追跡
    - 記録時の JST 時刻（時・分）も保持
    - マップ画面フッターの JST 時刻の 1 行上に表示
    - 両者が同値の場合は全時間最大のみ表示（冗長表示を抑制）
    - 異なる場合は「5分保持値@時刻 全時間最大値@時刻」の2項目表示
2026-03-13 0.905
    ・DOPログ追加
    ・電圧低下時の電圧を修正。低電圧の警告音の再生ボリュームを強制。
2026-03-13 0.906
    ・Slow opening demo bug fix
    ・README update
2026-03-18 0.91 BNO085 IMU の Kalman バリオ統合・Euler角ログ・Vario詳細画面・処理時間計測を追加し、アーキテクチャを整備した。
    1. BNO085 IMU 統合（Core0バリオメーター）
    GPS_TFT_map.ino の loop() に imu_update() / imu_kalman_baro_update() を追加し、BNO085+MS5611 Kalman融合バリオが動作するようになった
    airdata_wire_begin() を airdata.cpp から独立させ、I2Cバス初期化を imu_setup() より先に呼ぶ構成に変更（BNO085のブート順序保証）
    I2Cクロックを 100kHz → 400kHz に変更（BNO085の起動時クロックストレッチング対応）
    setup() 内のセンサー初期化順序を TFT→IMU→Airdata
2026-03-22 v0.911 — TRACKUP自機位置の下寄り化・GPS fix/HDOP状態別マーカー・トーン非ブロッキング化・SD初期化完了通知の4本柱。
    0.911: TRACKUP下寄り・HDOP不確かさ円・トーン非ブロッキング化・SD初期化完了通知
    ■ display_tft.cpp / .h
    - TRACKUP モードで自機Y位置を画面中央(cy=120)から下3/4(cy=180)に変更し、
    前方視界を広げた（get_self_cy() / get_needle_len() で一元管理）
    - GPS fix なし → グレーの × (draw_nofix_cross())
    HDOP ≥ 5.0 → 青い不確かさ円 (draw_hdop_circle()) を表示。
2026-03-23 vario_inhibit フラグ・Kalman係数のSD永続化・スタートアップデモ改善
    Description
    1. vario_inhibit フラグ追加
    settings.txt に vario_inhibit=true を書くことでバリオを完全無効化できる新フラグを追加
    音（update_vario()）・VSI描画（draw_vsi()/push_backscreen()）・設定画面での音量変更、すべてをこのフラグでガード
    UIからは変更不可（設定画面に「Inhibited」と表示されるが操作できない）
    2. Kalman フィルター係数の SD 永続化
2026-03-24 v0.914 — UBXバイナリGPS移行・GNSS VSI/高度KF融合・音声ミックス再生・CSVログ刷新
    ## 概要
    NMEA テキスト受信を u-blox UBX バイナリ（NAV-PVT/SAT/DOP）へ全面移行し、
    それに伴う Kalman バリオの GNSS 速度観測融合・高精度マーカー表示・
    音声ミックス再生・CSV ログカラム変更を一括実装。
    ## 主な変更
    ### GPS（gps.cpp / gps.h） — 最大変更
2026-03-26 v0.915 — BNO085自動復旧・KF MSL高度・BSL高度表示・バリオ音再調整 [IMU] - BNO085 通信途絶を1秒タイムアウトで自動検出、HW NRSTリセットで1分レートの自動復旧を実装 (imu_try_recovery) - get_imu_alive() を追加（接続済み かつ 直近1秒以内データ受信）、update_vario() / draw_vsi() で使用 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
2026-03-27 Update settings.h
    Volume調整
2026-03-28 0.916 PONS v6 RELEASE VERSION
    CPU温度のSD保存を追加
2026-03-28 case 3D model for v6
    ・Removed case for v4 and v5 (Seek branch for older version please)
    ・Added v6 case 3D print data
    ・Removed unnecessary log2.txt file.
2026-03-28 Kicad data for PONS v6 upload
    ・Removed v5 Kicad data (Refer Branch for v5)
    ・Add all v6 Kicad data.
2026-03-28 Add GNSS board kicad data.
2026-03-29 v6 説明書追加
    v1-v4説明書削除。Refer Branch.
2026-04-05 FPC connector upload
    FPC connector between boards
2026-04-16 Enhance README with new images and project details
    Added images and updated project overview in README.
